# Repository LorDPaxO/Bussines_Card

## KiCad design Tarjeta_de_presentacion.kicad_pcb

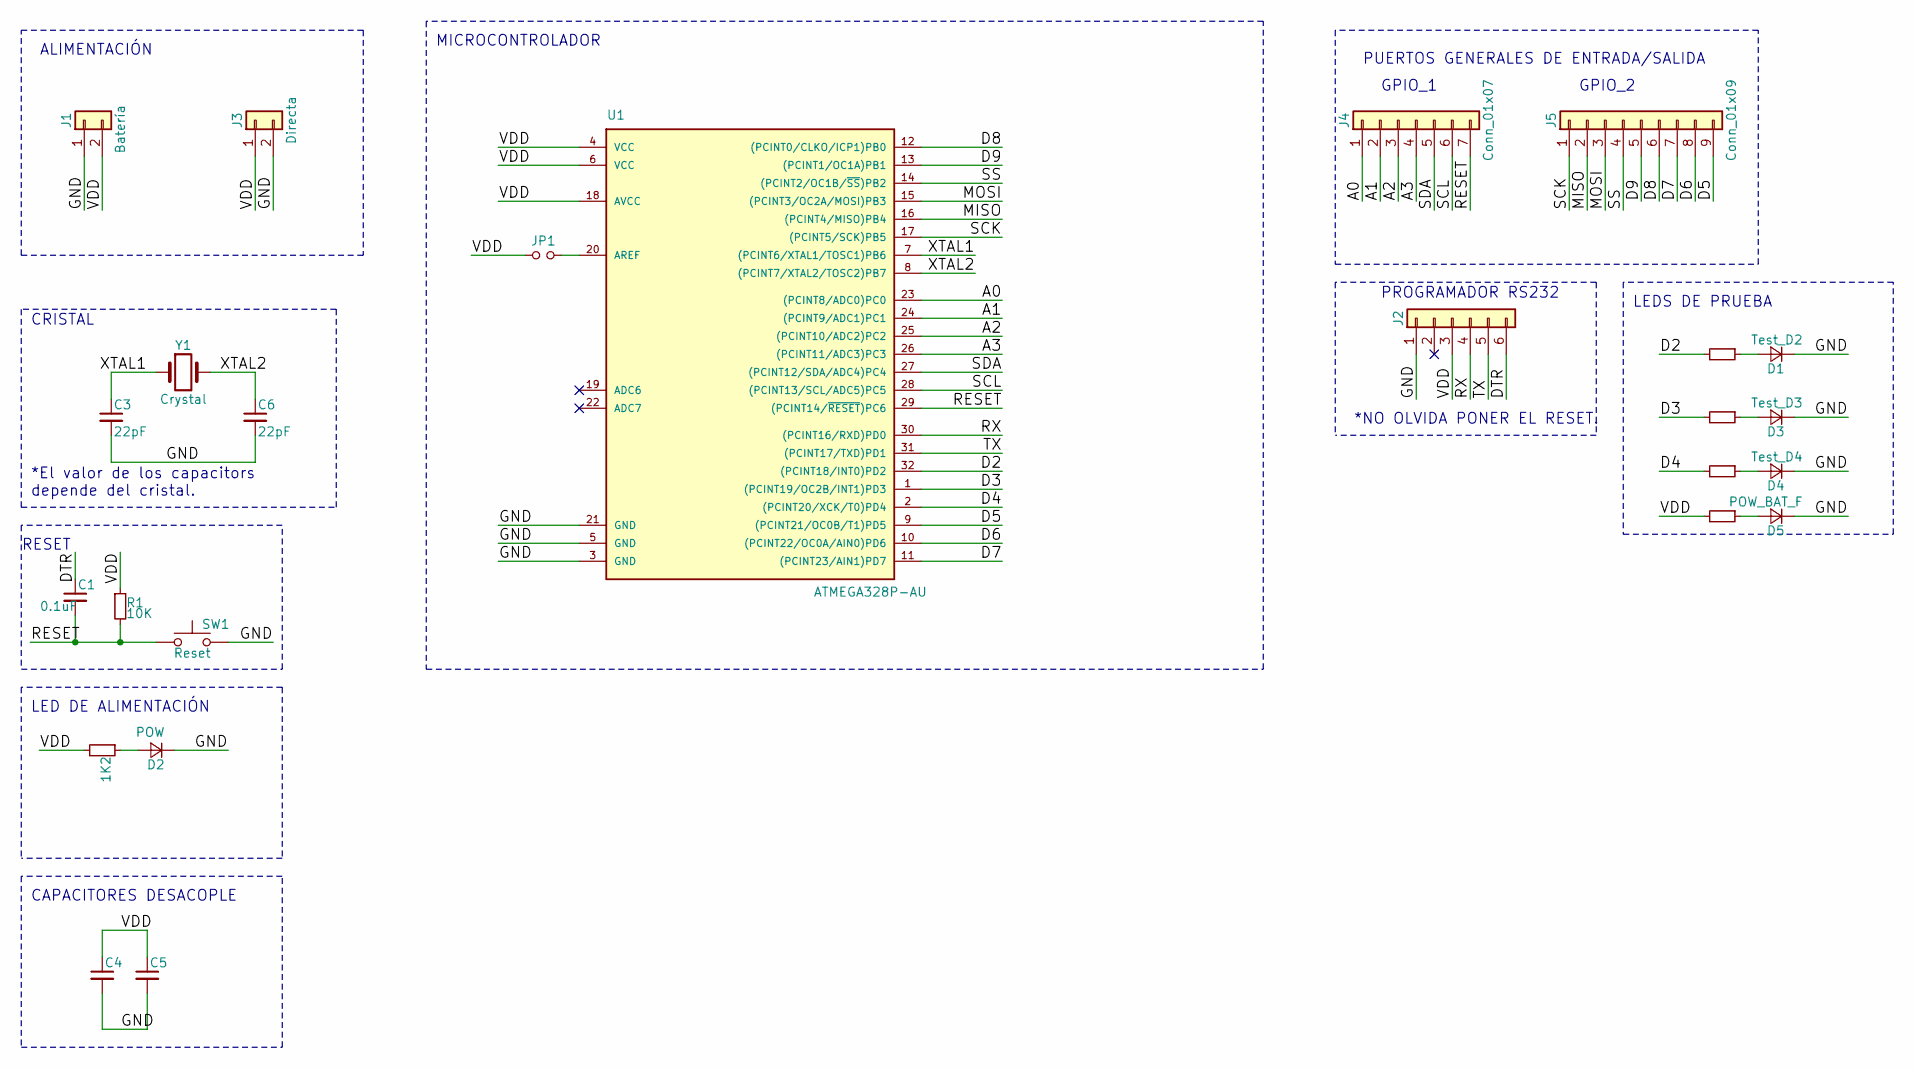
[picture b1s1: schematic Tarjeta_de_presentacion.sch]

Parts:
1K1, 1K2, 1K3, 1K4, 1K5: R_Small; R_0805_HandSoldering
C1: 0.1uF; C_0805_HandSoldering
C3, C6: 22pF; C_0805_HandSoldering
C4, C5: C_Small; C_0805_HandSoldering
D1: Test_D2; D_0805
D2: POW; D_0805
D3: Test_D3; D_0805
D4: Test_D4; D_0805
D5: POW_BAT_F; D_0805
J1: Batería; Holder_Battery
J2: Conn_01x06; Pin_Header_Straight_1x06_Pitch2.54mm
J3: Directa; Conector_Directo_SMD
J4: Conn_01x07; Pin_Header_Straight_1x07_Pitch2.54mm
J5: Conn_01x09; Pin_Header_Straight_1x09_Pitch2.54mm
JP1: Jumper_NO_Small; C_0805_HandSoldering
R1: 10K; R_0805_HandSoldering
SW1: Reset; Boton_Single
U1: ATMEGA328P-AU; TQFP-32_7x7mm_Pitch0.8mm
Y1: Crystal; Crystal_HC49-4H_Vertical

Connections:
/A0: J4.1, U1.23 ((PCINT8/ADC0)PC0)
/A1: J4.2, U1.24 ((PCINT9/ADC1)PC1)
/A2: J4.3, U1.25 ((PCINT10/ADC2)PC2)
/A3: J4.4, U1.26 ((PCINT11/ADC3)PC3)
/D2: 1K1.2, U1.32 ((PCINT18/INT0)PD2)
/D3: 1K3.2, U1.1 ((PCINT19/OC2B/INT1)PD3)
/D4: 1K4.2, U1.2 ((PCINT20/XCK/T0)PD4)
/D5: J5.9, U1.9 ((PCINT21/OC0B/T1)PD5)
/D6: J5.8, U1.10 ((PCINT22/OC0A/AIN0)PD6)
/D7: J5.7, U1.11 ((PCINT23/AIN1)PD7)
/D8: J5.6, U1.12 ((PCINT0/CLKO/ICP1)PB0)
/D9: J5.5, U1.13 ((PCINT1/OC1A)PB1)
/DTR: C1.1, J2.6
/GND: C3.2, C4.2, C5.2, C6.2, D1.1 (K), D2.1 (K), D3.1 (K), D4.1 (K), D5.1 (K), J1.1, J2.1, J3.2, SW1.2, U1.3 (GND), U1.5 (GND), U1.21 (GND)
/MISO: J5.2, U1.16 ((PCINT4/MISO)PB4)
/MOSI: J5.3, U1.15 ((PCINT3/OC2A/MOSI)PB3)
/RESET: C1.2, J4.7, R1.2, SW1.1, U1.29 ((PCINT14/~RESET~)PC6)
/RX: J2.4, U1.30 ((PCINT16/RXD)PD0)
/SCK: J5.1, U1.17 ((PCINT5/SCK)PB5)
/SCL: J4.6, U1.28 ((PCINT13/SCL/ADC5)PC5)
/SDA: J4.5, U1.27 ((PCINT12/SDA/ADC4)PC4)
/SS: J5.4, U1.14 ((PCINT2/OC1B/~SS~)PB2)
/TX: J2.5, U1.31 ((PCINT17/TXD)PD1)
/VDD: 1K2.2, 1K5.2, C4.1, C5.1, J1.2, J2.3, J3.1, JP1.1, R1.1, U1.4 (VCC), U1.6 (VCC), U1.18 (AVCC)
/XTAL1: C3.1, U1.7 ((PCINT6/XTAL1/TOSC1)PB6), Y1.1
/XTAL2: C6.1, U1.8 ((PCINT7/XTAL2/TOSC2)PB7), Y1.2
unnamed: 1K1.1, D1.2 (A)
unnamed: 1K2.1, D2.2 (A)
unnamed: 1K3.1, D3.2 (A)
unnamed: 1K4.1, D4.2 (A)
unnamed: 1K5.1, D5.2 (A)
unnamed: JP1.2, U1.20 (AREF)

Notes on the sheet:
ALIMENTACIÓN
MICROCONTROLADOR
CRISTAL
*El valor de los capacitors depende del cristal.
RESET
LED DE ALIMENTACIÓN
CAPACITORES DESACOPLE
PROGRAMADOR RS232
*NO OLVIDA PONER EL RESET.
GPIO_1
GPIO_2
PUERTOS GENERALES DE ENTRADA/SALIDA
LEDS DE PRUEBA

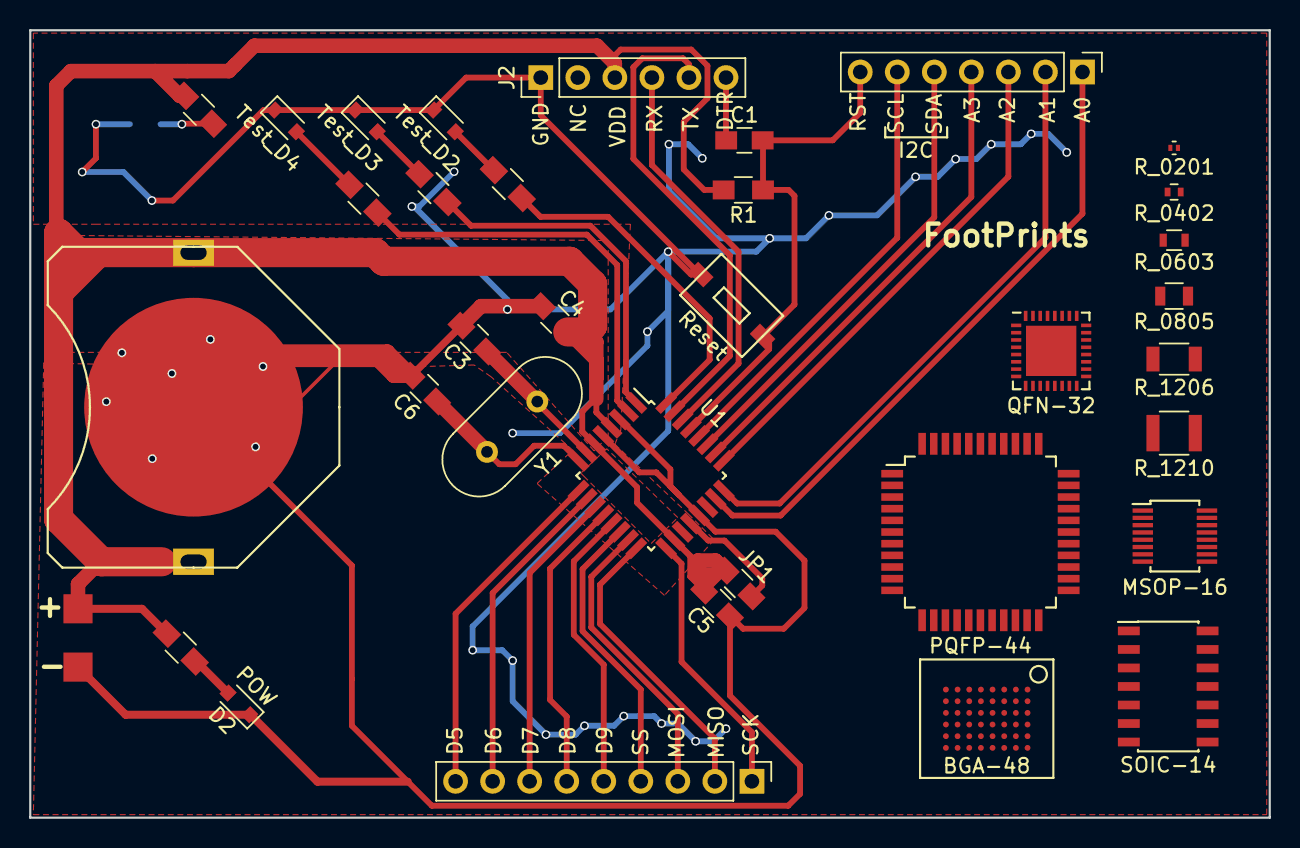
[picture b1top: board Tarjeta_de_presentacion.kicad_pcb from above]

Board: 2 copper layers, 85.0 x 54.0 mm, 25 parts (1 on the bottom side), 32 nets.

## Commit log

2018-05-29 //
    //
2018-06-03 /
    //
